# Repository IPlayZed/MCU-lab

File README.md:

# MCU-lab

## Overview

This repository is a collection of my projects written in my university's lab. We use Silicon Lab's [low cost board](https://www.silabs.com/development-tools/mcu/8-bit/efm8bb1lck-starter-kit). The examples are mostly written for the [extension board](4x7-segments%20Arduino%20shield-Eagle/). However they can be built on breadboards as well, but in some cases the layout of the components may be better suited to be built in a different way than it is in the [extension board](4x7-segments%20Arduino%20shield-Eagle/), resulting in different setups.

## Development environment

The development environment used is Silicon Lab's [Simplicity Studio 5](https://www.silabs.com/developers/simplicity-studio). This is an Eclipse based IDE, runs on all major OS platforms. It can be installed not only on Debian based systems, but Arch based ones as well from the [AUR](https://aur.archlinux.org/packages/simplicitystudio/). If using the latter version, Wine must be installed to use the Keil C51 compiler toolchain in the IDE for 8-bit development.

If you clone the project, if all is well, you can navigate to the actual development subfolders, where you can import it into the IDE.

## Project structure

I intend to keep subfolders on a per-lab basis, but this might change in the future. For detailed information on the given subproject, read the **README**.

When opening the project inside *Simplicity Studio 5*, you might want to import it to the same directory where you imported it from (thus you can still keep working in the cloned repository as your workspace), so I added a global `.gitignore` to not track project import reports.

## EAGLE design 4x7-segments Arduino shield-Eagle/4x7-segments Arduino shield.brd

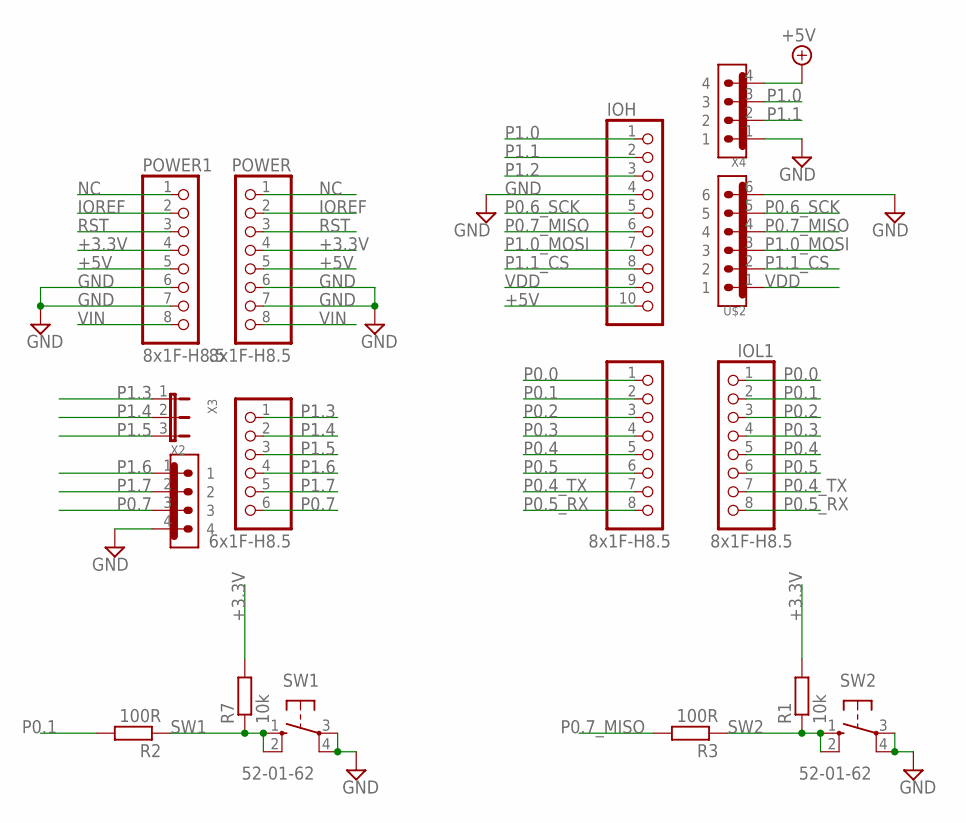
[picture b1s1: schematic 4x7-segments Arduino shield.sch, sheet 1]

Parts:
AD: 6x1F-H8.5; 1X06
IOH: 10x1F-H8.5; 1X10
IOL, IOL1: 8x1F-H8.5; 1X08
POWER, POWER1: 8x1F-H8.5; 1X08
R1, R7: 10k; R0805
R2, R3: 100R; R0805
SW1, SW2: 52-01-62; B3F-10XX
U$2: MOLEX6; MOLEXV6
X2, X4: MOLEX4V; MOLEXV4
X3: JP2E; JP2

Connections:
+3.3V: POWER.4, POWER1.4, R1.2, R7.2; also elsewhere on the board
+5V: IOH.10, POWER.5, POWER1.5, X4.4; also elsewhere on the board
GND: IOH.4, POWER.6, POWER.7, POWER1.6, POWER1.7, SW1.3, SW1.4 (P1), SW2.3, SW2.4 (P1), U$2.6, X2.4, X4.1; also elsewhere on the board
IOREF: POWER.2, POWER1.2
NC: POWER.1, POWER1.1
P0.0: IOL.1, IOL1.1; also elsewhere on the board
P0.1: IOL.2, IOL1.2, R2.2
P0.2: IOL.3, IOL1.3; also elsewhere on the board
P0.3: IOL.4, IOL1.4; also elsewhere on the board
P0.4: IOL.5, IOL1.5; also elsewhere on the board
P0.4_TX: IOL.7, IOL1.7
P0.5: IOL.6, IOL1.6
P0.5_RX: IOL.8, IOL1.8
P0.6_SCK: IOH.5, U$2.5
P0.7: AD.6, X2.3
P0.7_MISO: IOH.6, R3.2, U$2.4
P1.0: IOH.1, X4.3
P1.0_MOSI: IOH.7, U$2.3
P1.1: IOH.2, X4.2; also elsewhere on the board
P1.1_CS: IOH.8, U$2.2
P1.2: IOH.3; also elsewhere on the board
P1.3: AD.1, X3.1
P1.4: AD.2, X3.2
P1.5: AD.3, X3.3; also elsewhere on the board
P1.6: AD.4, X2.1
P1.7: AD.5, X2.2; also elsewhere on the board
RST: POWER.3, POWER1.3
SW1: R2.1, R7.1, SW1.1 (S), SW1.2 (S1)
SW2: R1.1, R3.1, SW2.1 (S), SW2.2 (S1)
VDD: IOH.9, U$2.1
VIN: POWER.8, POWER1.8

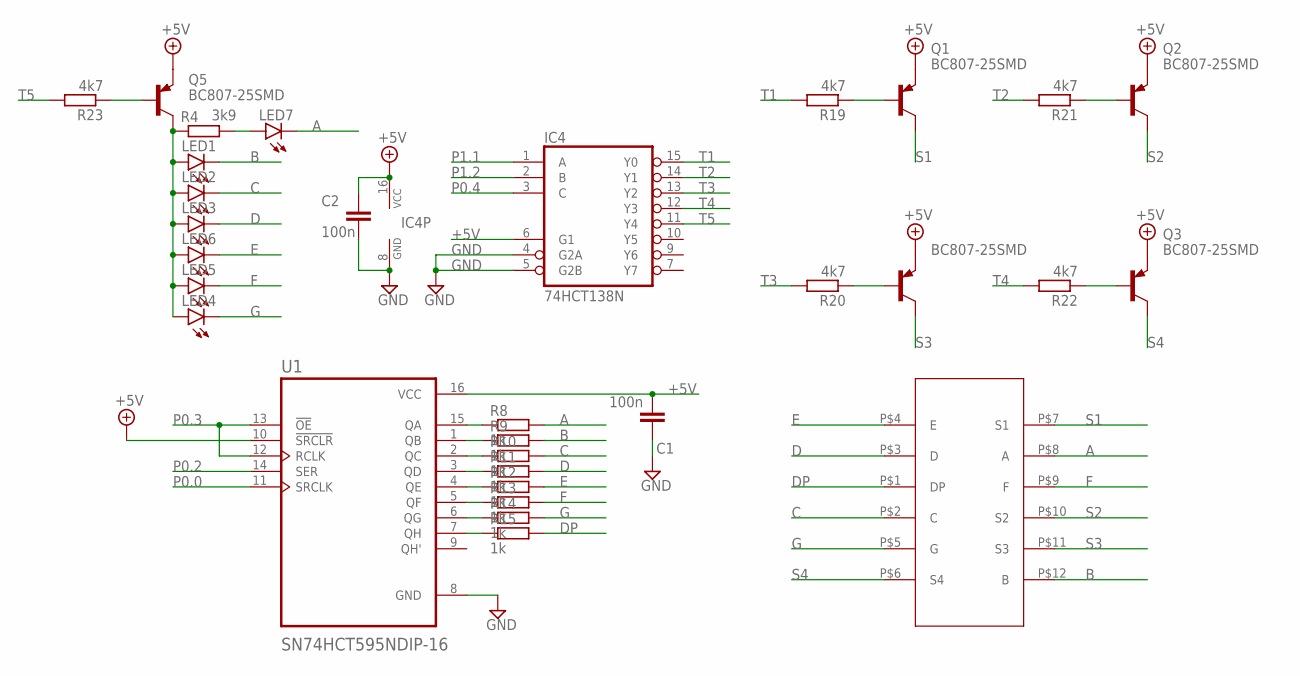
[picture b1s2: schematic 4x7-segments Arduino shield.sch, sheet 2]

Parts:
C1, C2: 100n; C0805
IC4: 74HCT138N; DIL16
LED1, LED2, LED3, LED4, LED5, LED6, LED7: LEDCHIPLED_1206; CHIPLED_1206
Q1, Q2, Q3, Q4, Q5: BC807-25SMD; SOT23-BEC
R4: 3k9; R1206
R8, R9, R10, R11, R12, R13, R14, R15: 1k; R1206
R19, R20, R21, R22, R23: 4k7; R0805
U1: SN74HCT595NDIP-16; DIP794W45P254L1969H508Q16
U$1: SH5461AS

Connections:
+5V: C1.1, C2.2, IC4.6 (G1), IC4.16 (VCC), Q1.E, Q2.E, Q3.E, Q4.E, Q5.E, U1.10 (!SRCLR), U1.16 (VCC); also elsewhere on the board
A: LED7.C, R8.2, U$1.P$8 (A)
B: LED1.C, R9.2, U$1.P$12 (B)
C: LED2.C, R10.2, U$1.P$2 (C)
D: LED3.C, R11.2, U$1.P$3 (D)
DP: R15.2, U$1.P$1 (DP)
E: LED6.C, R12.2, U$1.P$4 (E)
F: LED5.C, R13.2, U$1.P$9 (F)
G: LED4.C, R14.2, U$1.P$5 (G)
GND: C1.2, C2.1, IC4.4 (G2A), IC4.5 (G2B), IC4.8 (GND), U1.8 (GND); also elsewhere on the board
unnamed: R8.1, U1.15 (QA)
unnamed: R9.1, U1.1 (QB)
unnamed: R10.1, U1.2 (QC)
unnamed: R11.1, U1.3 (QD)
unnamed: R12.1, U1.4 (QE)
unnamed: R13.1, U1.5 (QF)
unnamed: R14.1, U1.6 (QG)
unnamed: R15.1, U1.7 (QH)
unnamed: Q1.B, R19.1
unnamed: Q4.B, R20.1
unnamed: Q2.B, R21.1
unnamed: Q3.B, R22.1
unnamed: LED1.A, LED2.A, LED3.A, LED4.A, LED5.A, LED6.A, Q5.C, R4.1
unnamed: Q5.B, R23.1
unnamed: LED7.A, R4.2
P0.0: U1.11 (SRCLK); also elsewhere on the board
P0.2: U1.14 (SER); also elsewhere on the board
P0.3: U1.12 (RCLK), U1.13 (!OE); also elsewhere on the board
P0.4: IC4.3 (C); also elsewhere on the board
P1.1: IC4.1 (A); also elsewhere on the board
P1.2: IC4.2 (B); also elsewhere on the board
S1: Q1.C, U$1.P$7 (S1)
S2: Q2.C, U$1.P$10 (S2)
S3: Q4.C, U$1.P$11 (S3)
S4: Q3.C, U$1.P$6 (S4)
T1: IC4.15 (Y0), R19.2
T2: IC4.14 (Y1), R21.2
T3: IC4.13 (Y2), R20.2
T4: IC4.12 (Y3), R22.2
T5: IC4.11 (Y4), R23.2

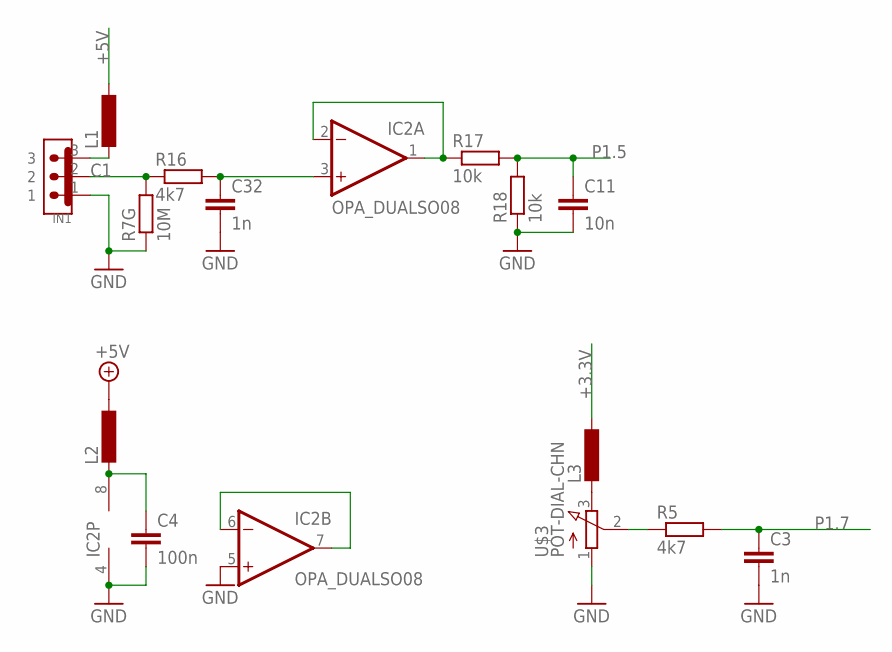
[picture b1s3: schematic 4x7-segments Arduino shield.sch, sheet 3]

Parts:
C3, C32: 1n; C0805
C4: 100n; C0805
C11: 10n; C0805
IC2: OPA_DUALSO08; SO08
IN1: MOLEX3V; MOLEXV3
L1, L2, L3: L0805; R0805
R5, R16: 4k7; R0805
R7G: 10M; R0805
R17, R18: 10k; R1206
U$3: POT-DIAL-CHN; POT5

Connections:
+3.3V: L3.2; also elsewhere on the board
+5V: L1.2, L2.2; also elsewhere on the board
C1: IN1.2, R7G.2, R16.1
GND: C3.1, C4.1, C11.1, C32.1, IC2.4 (V-), IC2.5 (+IN), IN1.1, R7G.1, R18.1, U$3.1 (A); also elsewhere on the board
unnamed: L3.1, U$3.3 (E)
unnamed: R5.1, U$3.2 (S)
unnamed: C32.2, IC2.3 (+IN), R16.2
unnamed: IN1.3, L1.1
unnamed: C4.2, IC2.8 (V+), L2.1
unnamed: IC2.6 (-IN), IC2.7 (OUT)
unnamed: IC2.1 (OUT), IC2.2 (-IN), R17.1
P1.5: C11.2, R17.2, R18.2; also elsewhere on the board
P1.7: C3.2, R5.2; also elsewhere on the board

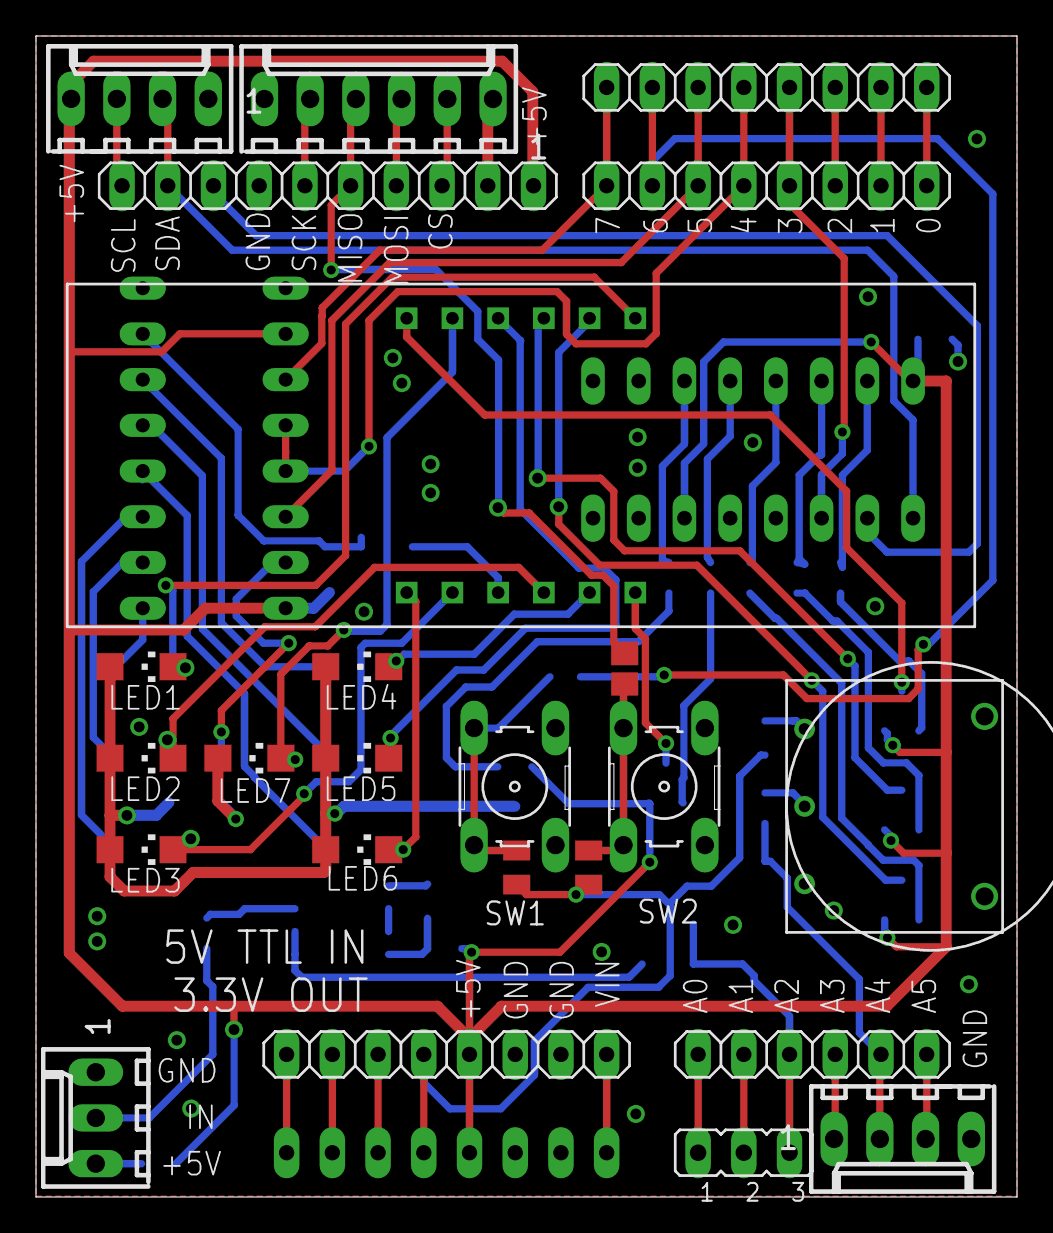
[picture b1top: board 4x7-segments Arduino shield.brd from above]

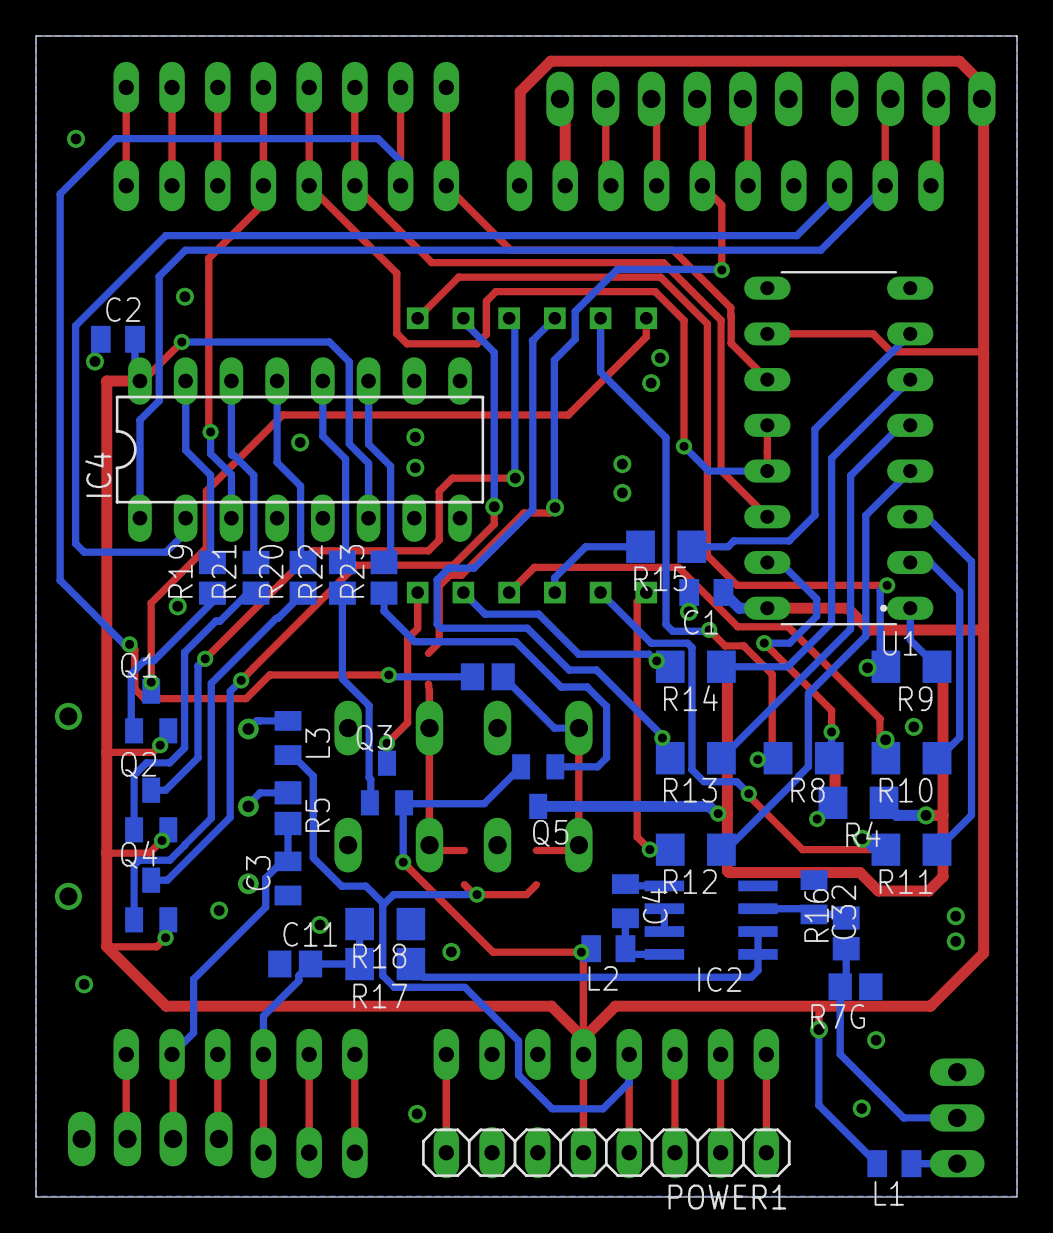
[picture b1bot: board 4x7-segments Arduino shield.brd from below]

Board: 2 copper layers, 54.5 x 64.5 mm, 62 parts (38 on the bottom side), 71 nets.

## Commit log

2021-09-28 Initial 04
2021-09-28 Initial config
2021-09-28 Changed portbit of potenciometer to good mode
2021-09-28 Setup of ADC config
2021-09-28 Changed potenciometer port mode to analog IO and skipped in the digital crossbar
2021-09-28 First version of excercie 01.
2021-09-28 Debugged, code is working.
2021-09-28 Added base project for 02.
2021-09-28 Config setup for 02.
2021-09-28 Testing example for mV conversion.
2021-09-28 Corrected mV scaling.
2021-09-28 02 correction.
2021-09-28 Try to fix push message error: src refspec main does not match any
2021-10-04 Added projects.
2021-10-05 05 base
2021-10-05 01 done
2021-10-12 06 Base
2021-10-12 01 base config
2021-10-12 Partly done 02.
2021-10-17 Added Eagle sketches for shield.
2021-10-25 Added project 06.
2021-10-25 Added project 07.
2021-10-25 Added 03.
2021-10-26 Test project.
2021-10-26 Added project README and gitignore.
2021-11-10 Added SPI related projects.
2021-11-10 Updated readme.
2021-11-23 Added project and renamed some things.
2021-11-23 Added PWM project.
2021-11-23 Corrected config.
2021-11-29 README updates.
2021-11-29 README refactoring
2021-11-29 Continued README for PCA/PWM.
2021-11-29 Continued writing PWM.
